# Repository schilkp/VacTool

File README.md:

# VacTool
### Philipp Schilk

A very simple PIC12F1572-based controller for a manual vacuum SMD component pick-and-place pen. 

# Description
Allows control of a 12Vdc solenoid valve and air pump using a 1/4" jack foot pedal.  
The solenoid is activated when the pedal is pressed. The operation of the pump is 
controlled by the position of the potentiometer:  

When the potentiometer is fully left, the pump follows the solenoid/foot pedal exactly.  

When the potentiometer is fully right, the pump runs continously.

In between, the pump will run when the solenoid is active, and will keep running for a while 
after the solenoid closes again determined by the potentiometer position. When continously
placing parts this should allow for a smoother workflow.

# Inspiration
Steve Gardner's (aka SDG Electronics) Vaccum Pick and Place Tool:  

[Youtube Video](https://www.youtube.com/watch?v=1FnGqH_WkL4)  

[Website](https://sdgelectronics.co.uk/youtube-videos/a-diy-smd-pick-and-place-tool-for-electronics-assembly/)

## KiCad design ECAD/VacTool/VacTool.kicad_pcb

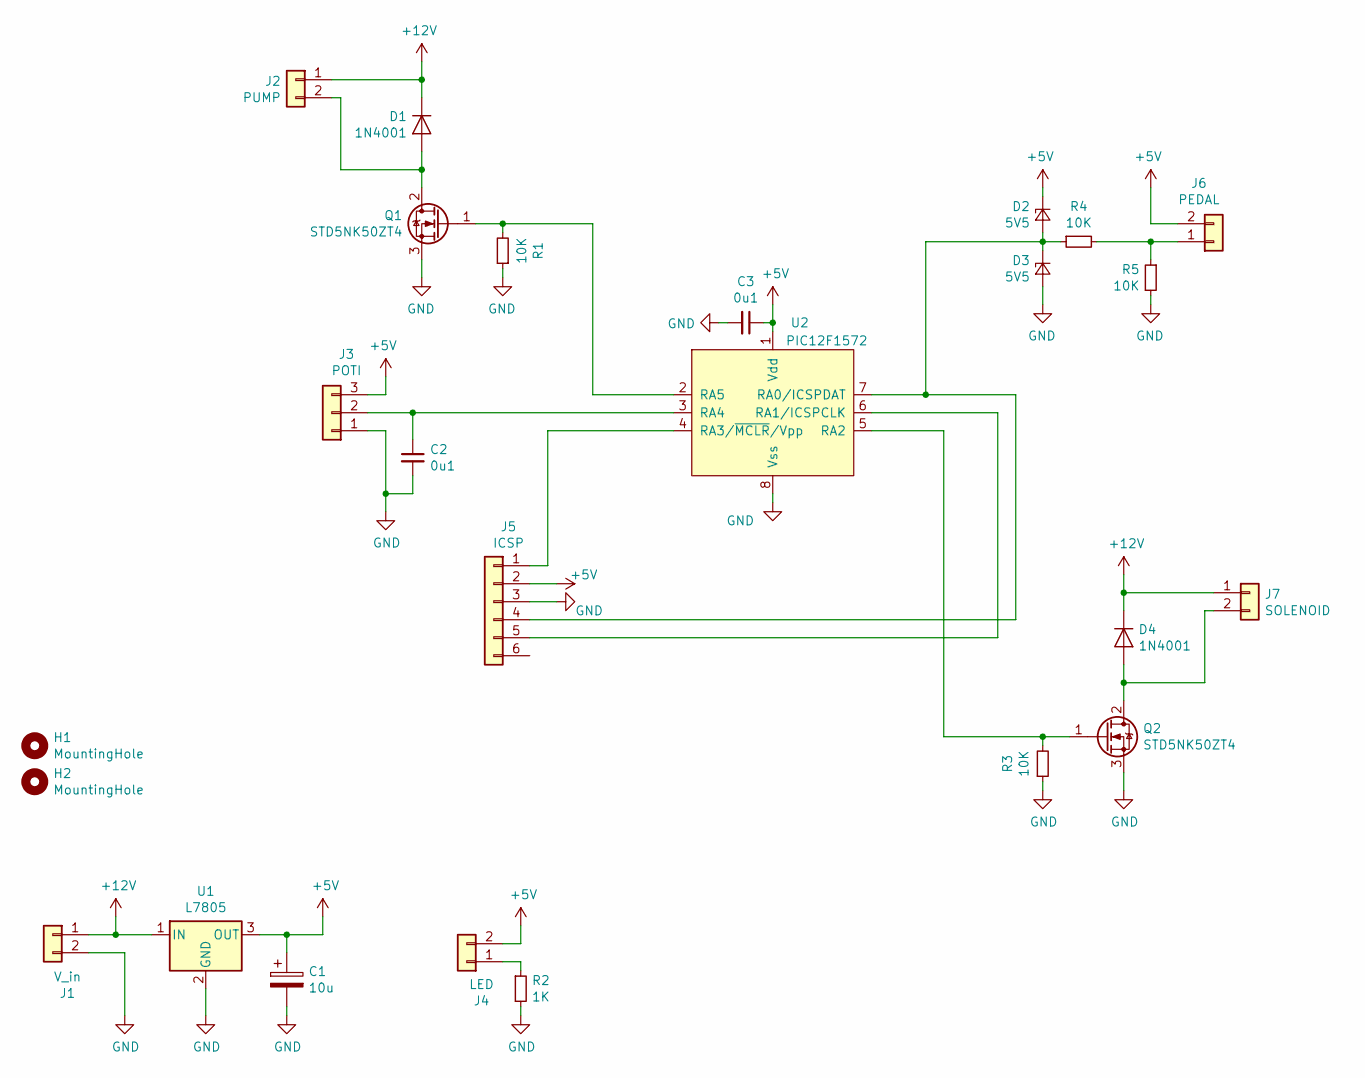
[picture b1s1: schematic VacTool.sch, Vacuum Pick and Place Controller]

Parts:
C1: 10u; CP_Elec_6.3x7.7
C2, C3: 0u1; C_0603_1608Metric
D1, D4: 1N4001; D_SOD-123F
D2, D3: 5V5; D_SOD-123
H1, H2: MountingHole; MountingHole_3.2mm_M3_Pad_Via
J1: V_in; TerminalBlock_Phoenix_MKDS-1,5-2_1x02_P5.00mm_Horizontal
J2: PUMP; TerminalBlock_Phoenix_MKDS-1,5-2_1x02_P5.00mm_Horizontal
J3: POTI; TerminalBlock_Phoenix_MKDS-1,5-3_1x03_P5.00mm_Horizontal
J4: LED; TerminalBlock_Phoenix_MKDS-1,5-2_1x02_P5.00mm_Horizontal
J5: ICSP; PinHeader_1x06_P2.54mm_Vertical
J6: PEDAL; TerminalBlock_Phoenix_MKDS-1,5-2_1x02_P5.00mm_Horizontal
J7: SOLENOID; TerminalBlock_Phoenix_MKDS-1,5-2_1x02_P5.00mm_Horizontal
Q1, Q2: STD5NK50ZT4; TO-252-2
R1, R3, R4, R5: 10K; R_0603_1608Metric
R2: 1K; R_0603_1608Metric
U1: L7805; TO-252-2
U2: PIC12F1572; SOIC-8_3.9x4.9mm_P1.27mm

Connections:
+5V: C1.1, C3.1, D2.1 (K), J3.3, J4.2, J5.2, J6.2, U1.3 (OUT), U2.1 (Vdd)
+12V: D1.1 (K), D4.1 (K), J1.1, J2.1, J7.1, U1.1 (IN)
GND: C1.2, C2.2, C3.2, D3.2 (A), J1.2, J3.1, J5.3, Q1.3 (S), Q2.3 (S), R1.1, R2.2, R3.1, R5.2, U1.2 (GND), U2.8 (Vss)
unnamed: C2.1, J3.2, U2.3 (RA4)
unnamed: D1.2 (A), J2.2, Q1.2 (D)
unnamed: D2.2 (A), D3.1 (K), J5.4, R4.1, U2.7 (RA0/ICSPDAT)
unnamed: D4.2 (A), J7.2, Q2.2 (D)
unnamed: J4.1, R2.1
unnamed: J5.1, U2.4 (RA3/~MCLR~/Vpp)
unnamed: J5.5, U2.6 (RA1/ICSPCLK)
unnamed: J6.1, R4.2, R5.1
unnamed: Q1.1 (G), R1.2, U2.2 (RA5)
unnamed: Q2.1 (G), R3.2, U2.5 (RA2)

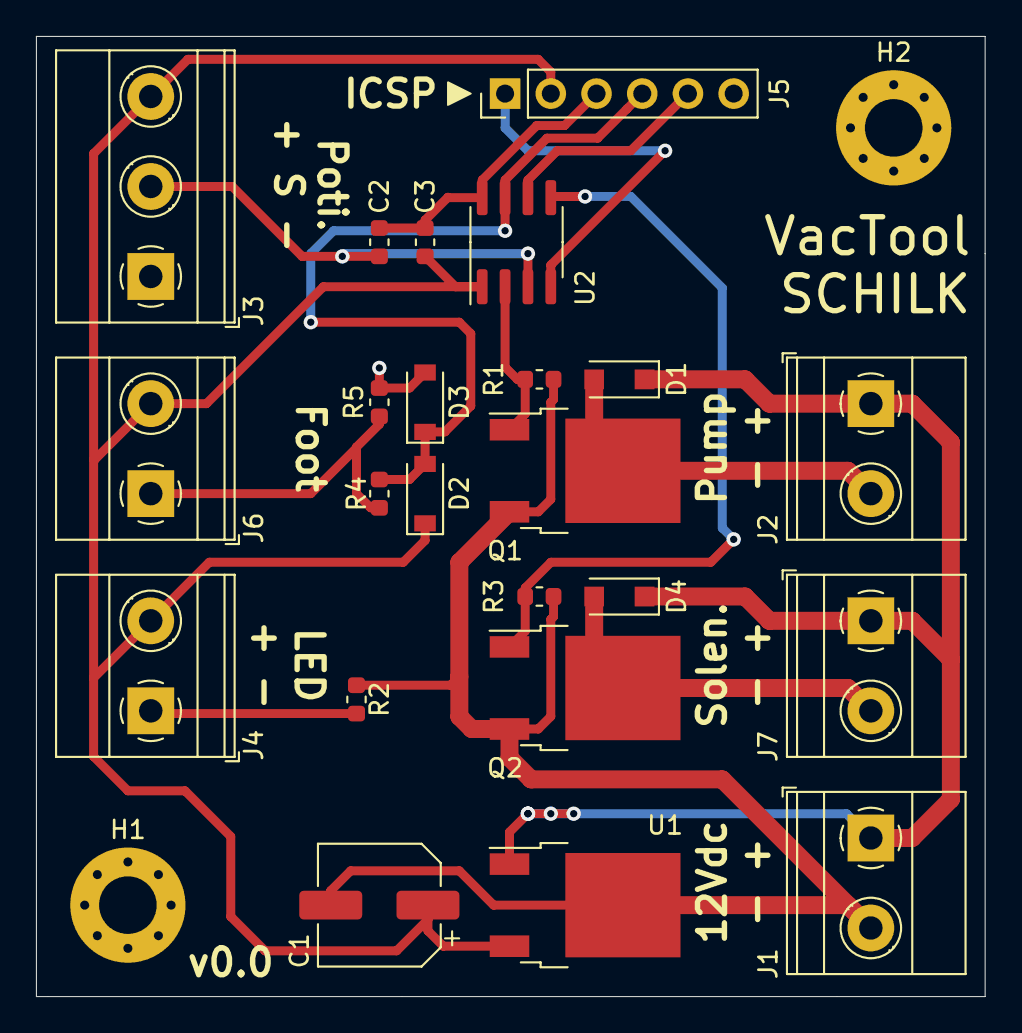
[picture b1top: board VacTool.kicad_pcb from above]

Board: 2 copper layers, 52.7 x 53.3 mm, 25 parts (0 on the bottom side), 13 nets.

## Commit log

2020-06-25 Initial v0.0 commit
2020-06-25 Added PCB render
2020-08-31 First draft firmware done and operational.
2020-08-31 Doc update.
2020-08-31 Created LICENSE
2020-08-31 Reorganised, added interactive BOM.
2020-08-31 Fixed Image Link.
2020-09-19 Readme typos
2021-05-24 Added .gitattributes
2021-09-13 Small Readme update
